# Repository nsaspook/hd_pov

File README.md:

# HD POV

hard drive disk strobe demo for pic18f1320 with cherry gs100502 gear sensor for
disk platter index (metal tab) detection.

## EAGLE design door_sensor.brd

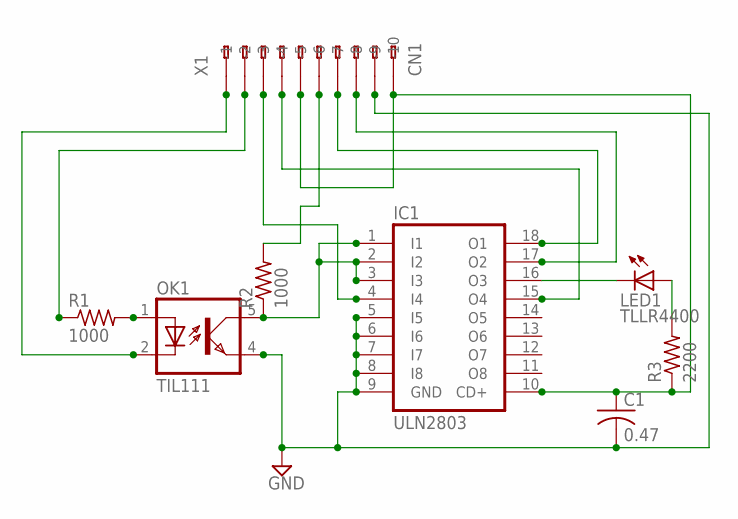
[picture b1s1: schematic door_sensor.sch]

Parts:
C1: 0.47; C025-024X044
IC1: ULN2803; DIL18
LED1: TLLR4400; LED3MM
OK1: TIL111; DIL06
R1, R2: 1000; 0204V
R3: 2200; 0204V
X1: CN1; 233-210

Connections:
GND: C1.2, IC1.5 (I5), IC1.6 (I6), IC1.7 (I7), IC1.8 (I8), IC1.9 (GND), OK1.4 (EMIT), X1.A9 (-9)
unnamed: OK1.1 (A), R1.2
unnamed: OK1.2 (C), X1.A1 (-1)
unnamed: IC1.4 (I4), X1.A3 (-3)
unnamed: IC1.1 (I1), IC1.2 (I2), IC1.3 (I3), OK1.5 (COL), R2.1
unnamed: IC1.15 (O4), X1.A4 (-4)
unnamed: R1.1, X1.A2 (-2)
unnamed: R2.2, X1.A6 (-6)
unnamed: IC1.18 (O1), X1.A7 (-7)
unnamed: IC1.17 (O2), X1.A8 (-8)
unnamed: LED1.A, R3.2
unnamed: C1.1, IC1.10 (CD+), R3.1, X1.A5 (-5), X1.A10 (-10)
unnamed: IC1.16 (O3), LED1.K (C)

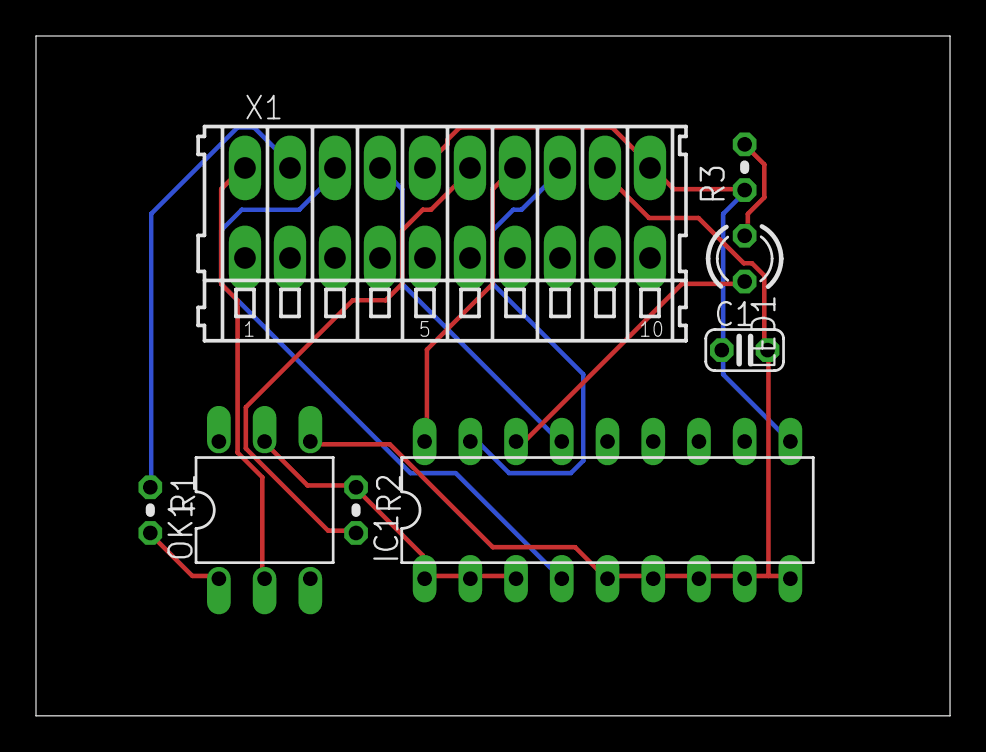
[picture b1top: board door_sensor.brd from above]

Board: 2 copper layers, 50.8 x 37.8 mm, 8 parts (0 on the bottom side), 13 nets.

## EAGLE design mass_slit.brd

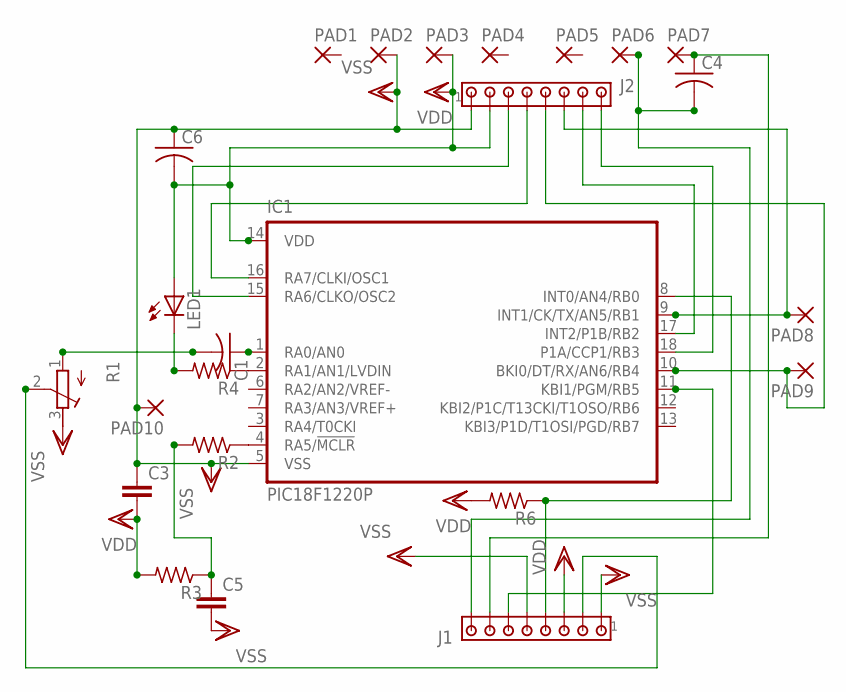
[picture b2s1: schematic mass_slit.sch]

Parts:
C1, C4, C6: C-US025-040X050; C025-040X050
C3, C5: C5/2.5; C5B2.5
IC1: PIC18F1220P; DIL18
J1, J2: MTA08-100; 10X08MTA
LED1: LED3MM
PAD1, PAD2, PAD3, PAD4, PAD5, PAD6, PAD7, PAD8, PAD9, PAD10: 1,6/0,9
R1: R-TRIMM3339P; RTRIM3339P
R2, R3, R4, R6: R-US_0204/2V; 0204V

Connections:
unnamed: IC1.10 (BKI0/DT/RX/AN6/RB4), J2.5, PAD9.1
unnamed: IC1.4 (RA5/!MCLR), R2.1
unnamed: C1.1, IC1.1 (RA0/AN0)
unnamed: C1.2, R1.1 (A)
unnamed: C4.1, J1.7, PAD7.1
unnamed: C4.2, J1.8, PAD6.1
unnamed: C5.1, R2.2, R3.1
unnamed: IC1.2 (RA1/AN1/LVDIN), R4.1
unnamed: IC1.8 (INT0/AN4/RB0), J1.4, R6.1
unnamed: J1.2, R1.2 (S)
unnamed: IC1.9 (INT1/CK/TX/AN5/RB1), J2.6, PAD8.1
unnamed: LED1.K (C), R4.2
unnamed: IC1.11 (KBI1/PGM/RB5), J1.6
unnamed: IC1.17 (INT2/P1B/RB2), J2.7
unnamed: IC1.18 (P1A/CCP1/RB3), J2.8
unnamed: IC1.16 (RA7/CLKI/OSC1), J2.4
unnamed: IC1.15 (RA6/CLKO/OSC2), J2.3
VDD: C3.2, C6.2, IC1.14 (VDD), J1.3, J2.2, LED1.A, PAD3.1, R3.2, R6.2
VSS: C3.1, C5.2, C6.1, IC1.5 (VSS), J1.1, J1.5, J2.1, PAD2.1, PAD10.1, R1.3 (E)

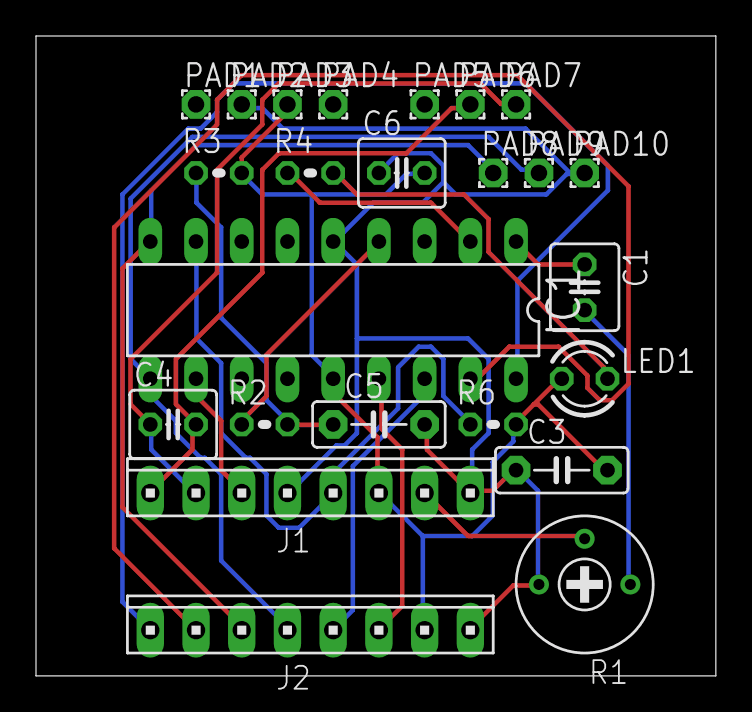
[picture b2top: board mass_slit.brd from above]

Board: 2 copper layers, 37.8 x 35.5 mm, 24 parts (0 on the bottom side), 19 nets.
